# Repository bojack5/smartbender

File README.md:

# smartbender
Maquina smartbender

##Lista de cosas por hacer

- [x] Conexion de Cilindros y PCB
- [x] Conexion de Nema42 a PCB y controlador
- [x] COnexion de Encoder 
- [x] Correccion de direccion debido a cambio de direccion encoder
- [ ] Maquinado de Guias
- [ ] Unidad FRL Nueva Mas grande
- [ ] Selecionar motor DC con encoder para dobladora
- [ ] Arreglar cortado de cizalla (posible mala nivelacion)
- [ ] Diseno de Pseudocodigo de control
- [ ] Rectificado de flecha dobladora
- [ ] Comprar presiostatos para cilindros chicos
- [x] Comprar balero 60x35x17 recto
- [ ] comprar agarraderas   
- [ ] Soldar tuercas a laminas
- [ ] cajas en lamina Inoxidable 
- [ ] Agujeros a cubierta para que siente 
- [ ] Integracion hardware-Software
- [ ] colocar Fines de carrera
- [ ] Conexion de fines de carrera
- [ ] colocar Homes motores
- [ ] conexion de homes

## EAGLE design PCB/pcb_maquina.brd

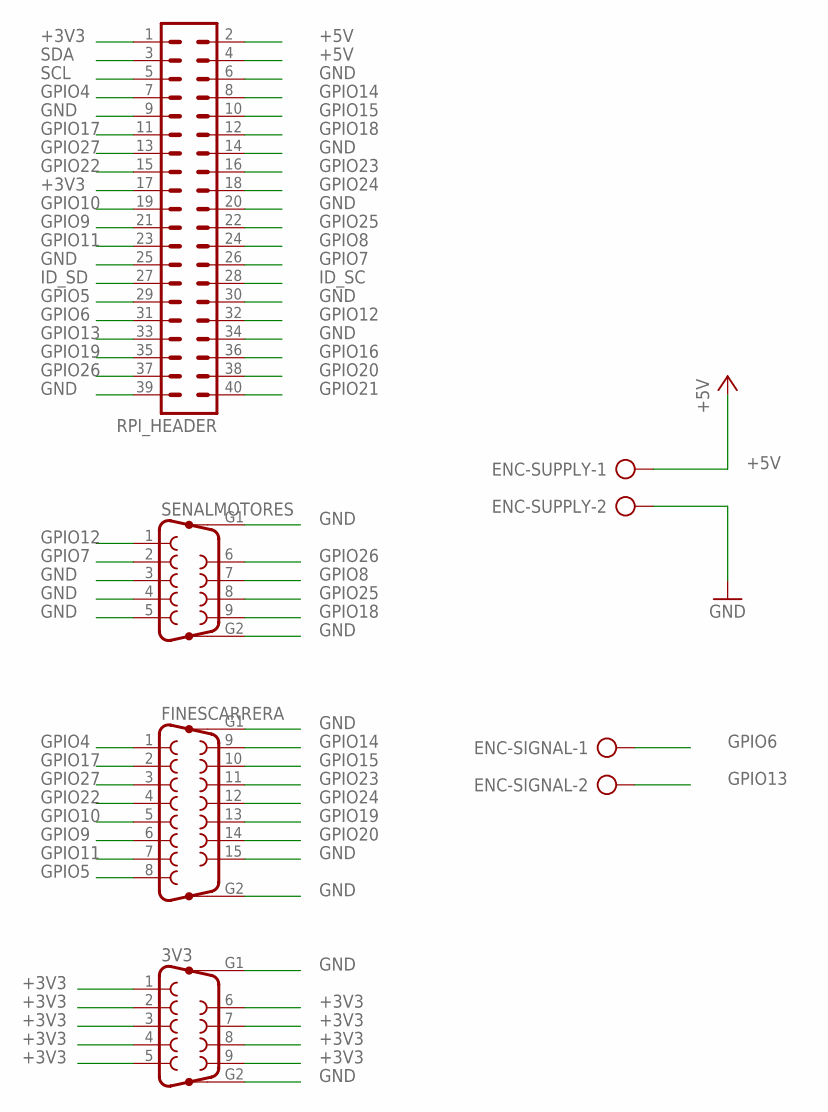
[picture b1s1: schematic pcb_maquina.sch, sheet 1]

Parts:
3V3: F09HP
ENC-SIGNAL: AK500/2
ENC-SUPPLY: AK500/2
FINESCARRERA: F15HP
RPI_HEADER: MA20-2
SENALMOTORES: F09HP

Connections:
+3V3: 3V3.1, 3V3.2, 3V3.3, 3V3.4, 3V3.5, 3V3.6, 3V3.7, 3V3.8, 3V3.9, RPI_HEADER.1, RPI_HEADER.17
+5V: ENC-SUPPLY.1, RPI_HEADER.2, RPI_HEADER.4; also elsewhere on the board
GND: 3V3.G1, 3V3.G2, ENC-SUPPLY.2, FINESCARRERA.15, FINESCARRERA.G1, FINESCARRERA.G2, RPI_HEADER.6, RPI_HEADER.9, RPI_HEADER.14, RPI_HEADER.20, RPI_HEADER.25, RPI_HEADER.30, RPI_HEADER.34, RPI_HEADER.39, SENALMOTORES.3, SENALMOTORES.4, SENALMOTORES.5, SENALMOTORES.G1, SENALMOTORES.G2; also elsewhere on the board
GPIO4: FINESCARRERA.1, RPI_HEADER.7
GPIO5: FINESCARRERA.8, RPI_HEADER.29
GPIO6: ENC-SIGNAL.1, RPI_HEADER.31
GPIO7: RPI_HEADER.26, SENALMOTORES.2
GPIO8: RPI_HEADER.24, SENALMOTORES.7
GPIO9: FINESCARRERA.6, RPI_HEADER.21
GPIO10: FINESCARRERA.5, RPI_HEADER.19
GPIO11: FINESCARRERA.7, RPI_HEADER.23
GPIO12: RPI_HEADER.32, SENALMOTORES.1
GPIO13: ENC-SIGNAL.2, RPI_HEADER.33
GPIO14: FINESCARRERA.9, RPI_HEADER.8
GPIO15: FINESCARRERA.10, RPI_HEADER.10
GPIO16: RPI_HEADER.36; also elsewhere on the board
GPIO17: FINESCARRERA.2, RPI_HEADER.11
GPIO18: RPI_HEADER.12, SENALMOTORES.9
GPIO19: FINESCARRERA.13, RPI_HEADER.35
GPIO20: FINESCARRERA.14, RPI_HEADER.38
GPIO21: RPI_HEADER.40; also elsewhere on the board
GPIO22: FINESCARRERA.4, RPI_HEADER.15
GPIO23: FINESCARRERA.11, RPI_HEADER.16
GPIO24: FINESCARRERA.12, RPI_HEADER.18
GPIO25: RPI_HEADER.22, SENALMOTORES.8
GPIO26: RPI_HEADER.37, SENALMOTORES.6
GPIO27: FINESCARRERA.3, RPI_HEADER.13
ID_SC: RPI_HEADER.28
ID_SD: RPI_HEADER.27
SCL: RPI_HEADER.5; also elsewhere on the board
SDA: RPI_HEADER.3; also elsewhere on the board

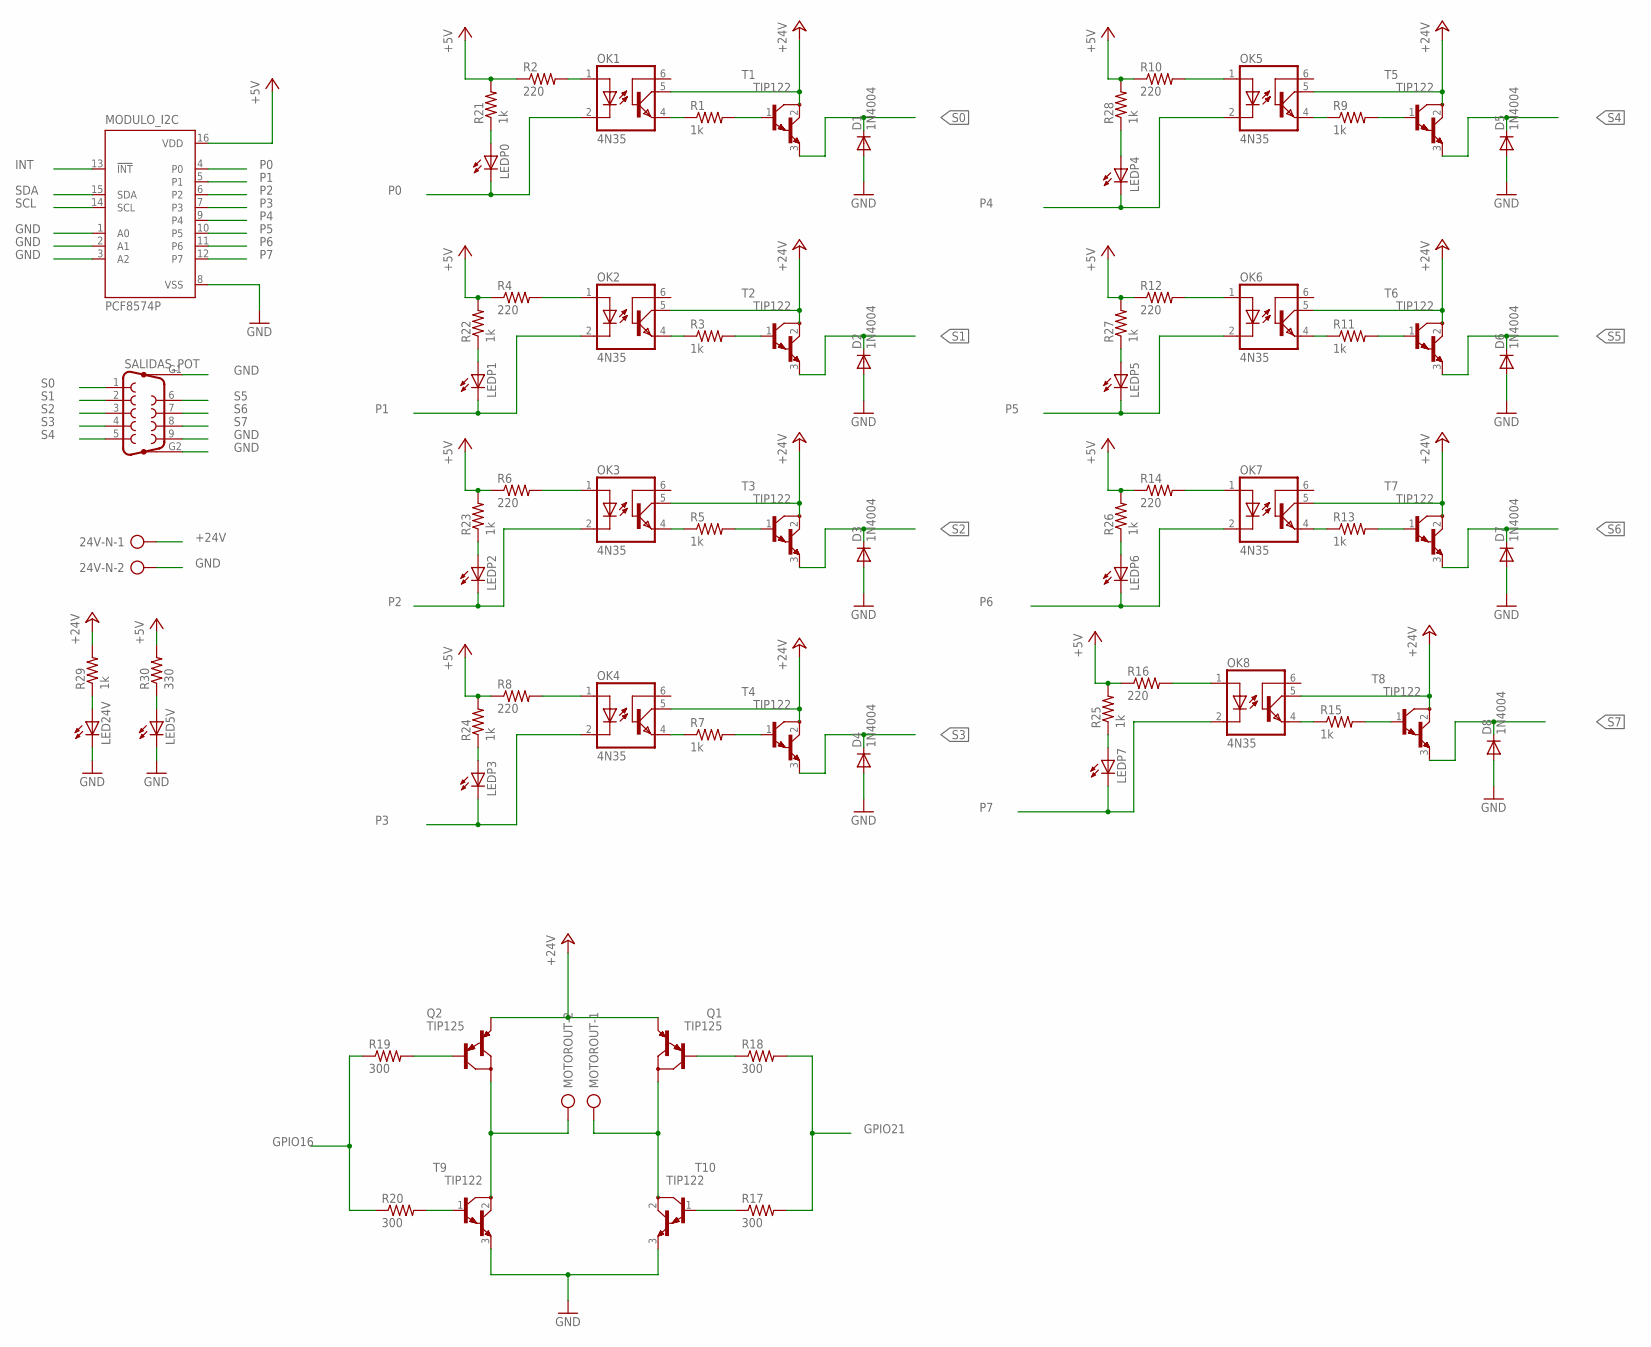
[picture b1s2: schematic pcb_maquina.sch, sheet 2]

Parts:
24V-N: AK300/2
D1, D2, D3, D4, D5, D6, D7, D8: 1N4004; DO41-10
LED5V, LED24V: LED3MM
LEDP0, LEDP1, LEDP2, LEDP3, LEDP4, LEDP5, LEDP6, LEDP7: LED3MM
MODULO_I2C: PCF8574P; DIL16
MOTOROUT: AK300/2
OK1, OK2, OK3, OK4, OK5, OK6, OK7, OK8: 4N35; DIL06
Q1, Q2: TIP125; TO220
R1, R3, R5, R7, R9, R11, R13, R15, R21, R22, R23, R24, R25, R26, R27, R28, R29: 1k; 0204/7
R2, R4, R6, R8, R10, R12, R14, R16: 220; 0204/7
R17, R18, R19, R20: 300; 0204/7
R30: 330; 0204/7
SALIDAS_POT: F09HP
T1, T2, T3, T4, T5, T6, T7, T8, T9, T10: TIP122; TO220

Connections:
+5V: MODULO_I2C.16 (VDD), R2.1, R4.1, R6.1, R8.1, R10.1, R12.1, R14.1, R16.1, R21.2, R22.2, R23.2, R24.2, R25.2, R26.2, R27.2, R28.2, R30.2; also elsewhere on the board
+24V: 24V-N.1, OK1.5 (COL), OK2.5 (COL), OK3.5 (COL), OK4.5 (COL), OK5.5 (COL), OK6.5 (COL), OK7.5 (COL), OK8.5 (COL), Q1.3 (E), Q2.3 (E), R29.2, T1.2 (C), T2.2 (C), T3.2 (C), T4.2 (C), T5.2 (C), T6.2 (C), T7.2 (C), T8.2 (C)
GND: 24V-N.2, D1.A, D2.A, D3.A, D4.A, D5.A, D6.A, D7.A, D8.A, LED5V.K (C), LED24V.K (C), MODULO_I2C.1 (A0), MODULO_I2C.2 (A1), MODULO_I2C.3 (A2), MODULO_I2C.8 (VSS), SALIDAS_POT.9, SALIDAS_POT.G1, SALIDAS_POT.G2, T9.3 (E), T10.3 (E); also elsewhere on the board
GPIO16: R19.1, R20.1; also elsewhere on the board
GPIO21: R17.2, R18.2; also elsewhere on the board
INT: MODULO_I2C.13 (!INT)
unnamed: OK1.1 (A), R2.2
unnamed: Q1.1 (B), R18.1
unnamed: Q2.1 (B), R19.2
unnamed: R20.2, T9.1 (B)
unnamed: MOTOROUT.2, Q2.2 (C), T9.2 (C)
unnamed: MOTOROUT.1, Q1.2 (C), T10.2 (C)
unnamed: LEDP0.A, R21.1
unnamed: R17.1, T10.1 (B)
unnamed: LEDP1.A, R22.1
unnamed: OK2.1 (A), R4.2
unnamed: LEDP2.A, R23.1
unnamed: OK1.4 (EMI), R1.1
unnamed: R1.2, T1.1 (B)
unnamed: LEDP3.A, R24.1
unnamed: LEDP4.A, R28.1
unnamed: OK2.4 (EMI), R3.1
unnamed: R3.2, T2.1 (B)
unnamed: LEDP5.A, R27.1
unnamed: OK3.1 (A), R6.2
unnamed: LEDP6.A, R26.1
unnamed: OK3.4 (EMI), R5.1
unnamed: R5.2, T3.1 (B)
unnamed: LEDP7.A, R25.1
unnamed: OK4.1 (A), R8.2
unnamed: LED5V.A, R30.1
unnamed: OK4.4 (EMI), R7.1
unnamed: R7.2, T4.1 (B)
unnamed: LED24V.A, R29.1
unnamed: OK5.1 (A), R10.2
unnamed: OK5.4 (EMI), R9.1
unnamed: R9.2, T5.1 (B)
unnamed: OK6.1 (A), R12.2
unnamed: OK6.4 (EMI), R11.1
unnamed: R11.2, T6.1 (B)
unnamed: OK7.1 (A), R14.2
unnamed: OK7.4 (EMI), R13.1
unnamed: R13.2, T7.1 (B)
unnamed: OK8.1 (A), R16.2
unnamed: OK8.4 (EMI), R15.1
unnamed: R15.2, T8.1 (B)
P0: LEDP0.K (C), MODULO_I2C.4 (P0), OK1.2 (C)
P1: LEDP1.K (C), MODULO_I2C.5 (P1), OK2.2 (C)
P2: LEDP2.K (C), MODULO_I2C.6 (P2), OK3.2 (C)
P3: LEDP3.K (C), MODULO_I2C.7 (P3), OK4.2 (C)
P4: LEDP4.K (C), MODULO_I2C.9 (P4), OK5.2 (C)
P5: LEDP5.K (C), MODULO_I2C.10 (P5), OK6.2 (C)
P6: LEDP6.K (C), MODULO_I2C.11 (P6), OK7.2 (C)
P7: LEDP7.K (C), MODULO_I2C.12 (P7), OK8.2 (C)
S0: D1.C, SALIDAS_POT.1, T1.3 (E)
S1: D2.C, SALIDAS_POT.2, T2.3 (E)
S2: D3.C, SALIDAS_POT.3, T3.3 (E)
S3: D4.C, SALIDAS_POT.4, T4.3 (E)
S4: D5.C, SALIDAS_POT.5, T5.3 (E)
S5: D6.C, SALIDAS_POT.6, T6.3 (E)
S6: D7.C, SALIDAS_POT.7, T7.3 (E)
S7: D8.C, SALIDAS_POT.8, T8.3 (E)
SCL: MODULO_I2C.14 (SCL); also elsewhere on the board
SDA: MODULO_I2C.15 (SDA); also elsewhere on the board

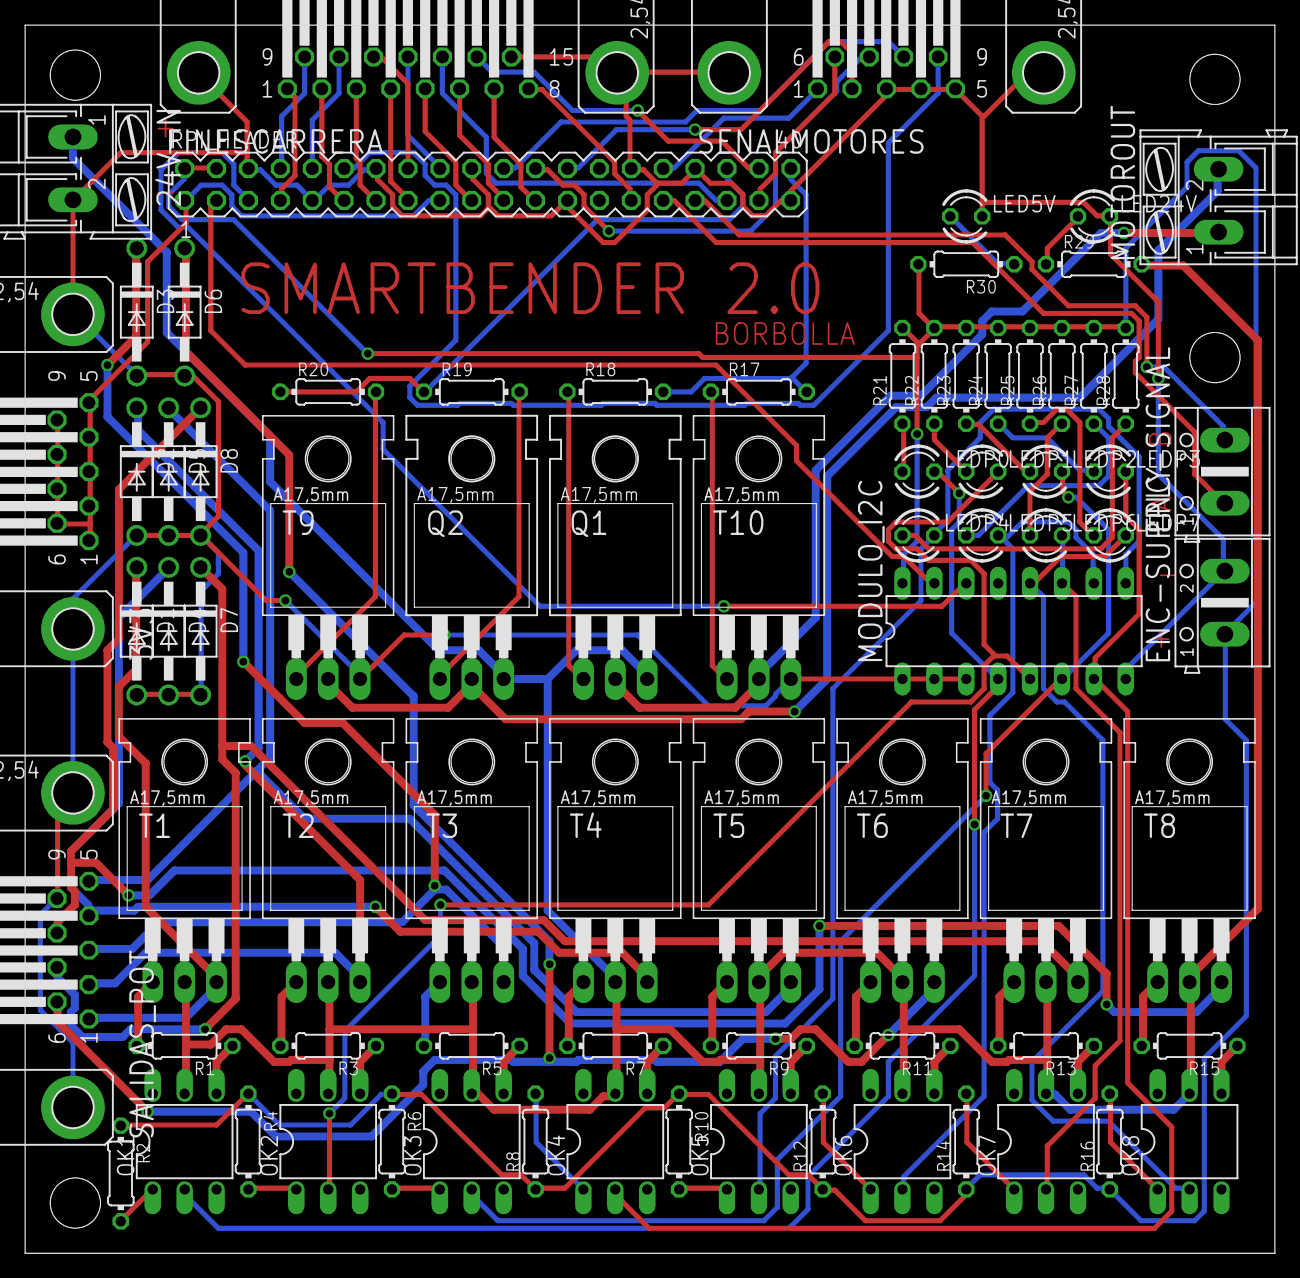
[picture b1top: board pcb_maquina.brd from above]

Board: 2 copper layers, 99.5 x 97.8 mm, 78 parts (0 on the bottom side), 86 nets.

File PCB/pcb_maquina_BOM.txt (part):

Partlist exported from /home/bojack/Documents/.smartbender/PCB/pcb_maquina.sch at 27/09/16 10:21 A.M.

Part         Value    Device      Package Description                       MF                      MPN       OC_FARNELL OC_NEWARK
3V3                   F09HP       F09HP   SUB-D                                                               unknown    unknown  
24V-N                 AK300/2     AK300/2 CONNECTOR                                                           unknown    unknown  
D1           1N4004   1N4004      DO41-10 DIODE                                                                                   
D2           1N4004   1N4004      DO41-10 DIODE                                                                                   
D3           1N4004   1N4004      DO41-10 DIODE                                                                                   
D4           1N4004   1N4004      DO41-10 DIODE                                                                                   
D5           1N4004   1N4004      DO41-10 DIODE                                                                                   
D6           1N4004   1N4004      DO41-10 DIODE                                                                                   
D7           1N4004   1N4004      DO41-10 DIODE                                                                                   
D8           1N4004   1N4004      DO41-10 DIODE                                                                                   
ENC-SIGNAL            AK500/2     AK500/2 CONNECTOR                                                           unknown    unknown  
ENC-SUPPLY            AK500/2     AK500/2 CONNECTOR                                                           unknown    unknown  
FINESCARRERA          F15HP       F15HP   SUB-D                                                               unknown    unknown  
LED5V                 LED3MM      LED3MM  LED                                                                                     
LED24V                LED3MM      LED3MM  LED                                                                                     
LEDP0                 LED3MM      LED3MM  LED                                                                                     
LEDP1                 LED3MM      LED3MM  LED                                                                                     
LEDP2                 LED3MM      LED3MM  LED                                                                                     
LEDP3                 LED3MM      LED3MM  LED                                                                                     
LEDP4                 LED3MM      LED3MM  LED                                                                                     
LEDP5                 LED3MM      LED3MM  LED                                                                                     
LEDP6                 LED3MM      LED3MM  LED                                                                                     
LEDP7                 LED3MM      LED3MM  LED                                                                                     
MODULO_I2C   PCF8574P PCF8574P    DIL16   I2C-Bus Remote 8-bit I/O expander                         PCF8574PN 204020     11N8515  
MOTOROUT              AK300/2     AK300/2 CONNECTOR                                                           unknown    unknown  
OK1          4N35     4N35        DIL06   MOTOROLA OPTO COUPLER             FAIRCHILD SEMICONDUCTOR 4N35      1328375    72K9946  
OK2          4N35     4N35        DIL06   MOTOROLA OPTO COUPLER             FAIRCHILD SEMICONDUCTOR 4N35      1328375    72K9946  
OK3          4N35     4N35        DIL06   MOTOROLA OPTO COUPLER             FAIRCHILD SEMICONDUCTOR 4N35      1328375    72K9946  
OK4          4N35     4N35        DIL06   MOTOROLA OPTO COUPLER             FAIRCHILD SEMICONDUCTOR 4N35      1328375    72K9946  
OK5          4N35     4N35        DIL06   MOTOROLA OPTO COUPLER             FAIRCHILD SEMICONDUCTOR 4N35      1328375    72K9946  
OK6          4N35     4N35        DIL06   MOTOROLA OPTO COUPLER             FAIRCHILD SEMICONDUCTOR 4N35      1328375    72K9946  
OK7          4N35     4N35        DIL06   MOTOROLA OPTO COUPLER             FAIRCHILD SEMICONDUCTOR 4N35      1328375    72K9946  
OK8          4N35     4N35        DIL06   MOTOROLA OPTO COUPLER             FAIRCHILD SEMICONDUCTOR 4N35      1328375    72K9946  
Q1           TIP125   TIP125      TO220   PNP Transistor                                                                          
Q2           TIP125   TIP125      TO220   PNP Transistor                                                                          
R1           1k       R-US_0204/7 0204/7  RESISTOR, American symbol                                                               
R2           220      R-US_0204/7 0204/7  RESISTOR, American symbol                                                               
R3           1k       R-US_0204/7 0204/7  RESISTOR, American symbol                                                               
R4           220      R-US_0204/7 0204/7  RESISTOR, American symbol                                                               
R5           1k       R-US_0204/7 0204/7  RESISTOR, American symbol                                                               
R6           220      R-US_0204/7 0204/7  RESISTOR, American symbol                                                               
R7           1k       R-US_0204/7 0204/7  RESISTOR, American symbol                                                               
R8           220      R-US_0204/7 0204/7  RESISTOR, American symbol                                                               
R9           1k       R-US_0204/7 0204/7  RESISTOR, American symbol                                                               
R10          220      R-US_0204/7 0204/7  RESISTOR, American symbol                                                               
R11          1k       R-US_0204/7 0204/7  RESISTOR, American symbol                                                               
R12          220      R-US_0204/7 0204/7  RESISTOR, American symbol                                                               
R13          1k       R-US_0204/7 0204/7  RESISTOR, American symbol                                                               
R14          220      R-US_0204/7 0204/7  RESISTOR, American symbol                                                               
R15          1k       R-US_0204/7 0204/7  RESISTOR, American symbol                                                               
R16          220      R-US_0204/7 0204/7  RESISTOR, American symbol                                                               
R17          300      R-US_0204/7 0204/7  RESISTOR, American symbol                                                               
R18          300      R-US_0204/7 0204/7  RESISTOR, American symbol                                                               
R19          300      R-US_0204/7 0204/7  RESISTOR, American symbol                                                               
R20          300      R-US_0204/7 0204/7  RESISTOR, American symbol                                                               
R21          1k       R-US_0204/7 0204/7  RESISTOR, American symbol                                                               
R22          1k       R-US_0204/7 0204/7  RESISTOR, American symbol                                                               
R23          1k       R-US_0204/7 0204/7  RESISTOR, American symbol                                                               
R24          1k       R-US_0204/7 0204/7  RESISTOR, American symbol                                                               
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
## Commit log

2016-02-04 qwerty
2016-02-04 primer migrate
2016-02-17 stepper funcionando
2016-02-18 cilindro funcionando
2016-02-19 Prueba escalonada
2016-02-19 Prueba lineal
2016-02-22 codigo pid simple
2016-04-05 cilindros binarios con PCF
2016-04-05 Toggle y reset funcionando con PCF y Rele
2016-04-12 Cilindros Sencillos y dobles , acomodados por clases , y con archivo de configuracion
2016-04-13 Clases Nema 23 y 42 con enable y pines a declarar
2016-04-15 cambios varios
2016-04-15 agregado de pasos a funcion Nema42
2016-04-15 Programa principal para stepper , inicio nema 42
2016-04-15 Nema42 funcionando con principal
2016-04-19 codigo para encoder
2016-04-20 programas simples para pruebas
2016-04-20 Ecoder 2 lados
2016-04-22 prueba encoder pigpio
2016-04-23 1 intento de pigpio con 2 interrupciones para encoder
2016-04-25 prueba de encoder sin prints
2016-04-26 prueba rotary encoder
2016-04-26 Operaciones con nema42
2016-04-26 velocidad en encoder mecanico
2016-04-26 Rampa stepper
2016-04-27 rampa de aceleracion
2016-04-27 Primera prueba de conversion de tus a pulsos con frecuencia
2016-04-29 Pre3paracion imports para clase de PID velocidad :O
2016-04-29 PID Velocidad version 1.0
2016-05-16 arreglo de tabs e indentacion
2016-05-16 Grafica Prueba PRBS
2016-05-17 Encoder y motor funcionando (Encoder como una sola clase , con la funcion embebida en ella misma como self)
2016-05-17 PID Velocidad 1.0
2016-05-17 callback de PID fuera
2016-05-17 callback pid fuera
2016-05-18 Cambio de direccion PID
2016-05-18 pruebas varias
2016-05-18 antes de irme ig
2016-05-18 escritura de datos
2016-05-18 Sintonizado default PID Velocidad
2016-05-18 Pruebas PRBS con log
2016-05-18 Prueba de datos prbs para graficar
2016-05-18 datos log de prbs
2016-05-18 Agregado de direccion a velocidad
2016-05-18 prueba prbs con 10 mm/s
2016-05-19 Correccion de pid de velocidad con callback en PID y no en encoder
2016-05-19 pruebas PRBS buenas
2016-05-20 datos prbs
2016-05-20 prbs
2016-05-20 valored prbs2
2016-05-20 ajustes listos para PID POsicion
2016-05-20 PID posicion 1.0
2016-05-20 pid Posicion 1.1
2016-05-21 PID Posicion con lazo abierto de velocidad
2016-05-21 PID Posicion
2016-05-21 pid funcionando
2016-05-23 grafica pid velocidad
2016-05-23 graficas velocidad
2016-05-23 Valores PID Posicion 10,50,100
2016-05-23 valores pid corregidos
2016-05-23 grafica continua
2016-06-10 cambios de direccion para nueva posicion del encoder
2016-06-10 respaldo antes de ip estatico
2016-06-10 checklist
2016-06-14 compra de balero
2016-06-17 comienzo de programa de prueba
2016-06-20 Primer letra F
2016-06-21 Prueba de matriz con m1 , m2 y prensa
2016-06-23 Try - Except agregado
2016-07-29 sincronizacion varios
2016-08-05 Agregado de PCB sche y brd
2016-09-27 BOM list
